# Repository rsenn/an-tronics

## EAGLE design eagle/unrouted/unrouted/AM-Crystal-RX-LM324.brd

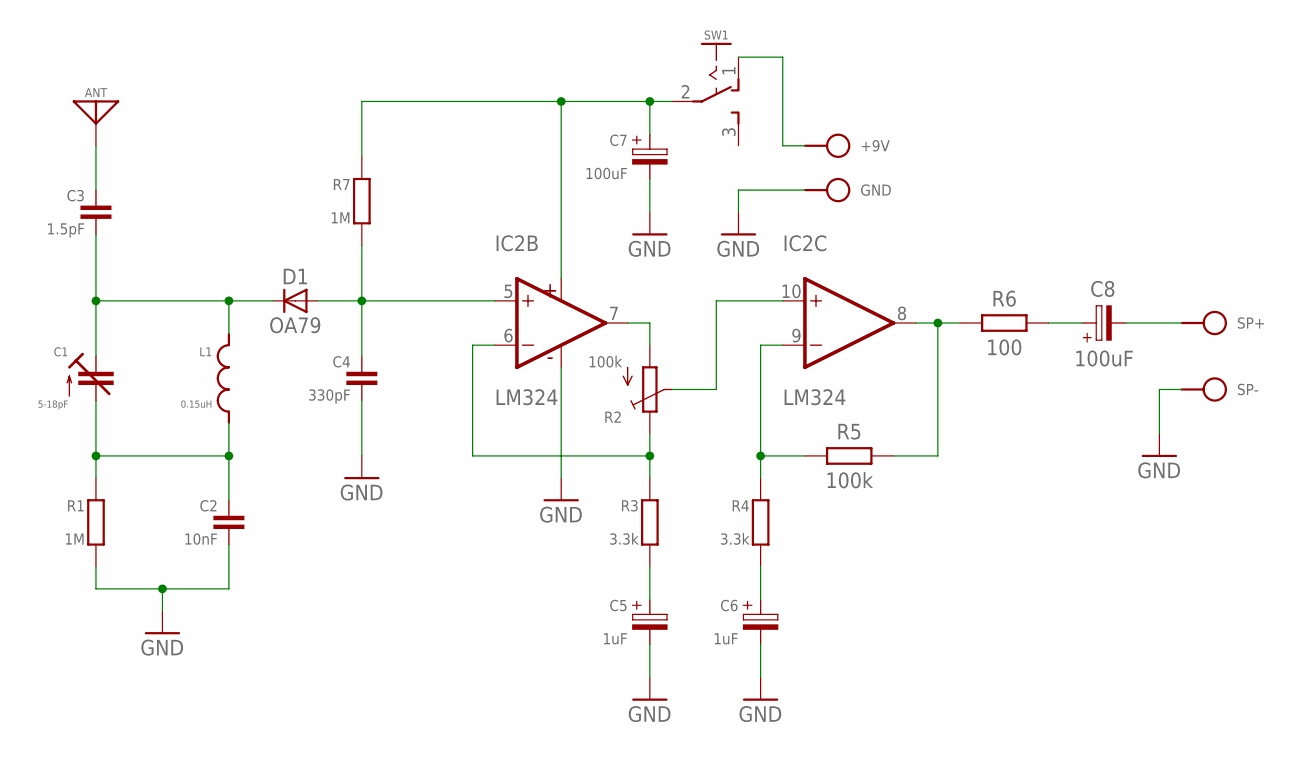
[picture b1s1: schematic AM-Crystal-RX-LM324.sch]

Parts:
+9V: BAT+; SPAD
ANT: ANT; SPAD
C1: 5-18pF; TRIM-2222-808
C2: 10nF; C050-025X075/V
C3: 1.5pF; C050-020X036
C4: 330pF; C050-024X044/V
C5: 1uF; E2.5-4/V
C6: 1uF; E2,5-3/V
C7: 100uF; E5-5/V
C8: 100uF; E2,5-5/V
D1: OA79; OA79-18/V
GND: BAT-; SPAD
IC2: LM324; DIL14
L1: 0.15uH; L-04-5/5
R1, R7: 1M; 0202/7-V
R2: 100k; B64Y
R3: 3.3k; 0202/7
R4: 3.3k; 0202/7-V
R5: 100k; 0202/7-V
R6: 100; 0202/7-V
SP+: SPKR+; SPAD
SP-: SPKR-; SPAD
SW1: SL-SW-1P-2T-H; SLSW-1P2T-H

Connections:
A: IC2.7 (OUT), R2.A
E: IC2.6 (-IN), R2.E, R3.1
GND: C2.2, C4.2, C5.-, C6.-, C7.-, GND.1, IC2.11 (V-), R1.2, SP-.1
unnamed: C4.1, D1.A, IC2.5 (+IN), R7.2
unnamed: C7.+, IC2.4 (V+), R7.1, SW1.2
unnamed: C1.1 (A), C2.1, L1.1, R1.1
unnamed: C1.2 (E), C3.2, D1.C, L1.2
unnamed: ANT.1, C3.1
unnamed: IC2.8 (OUT), R5.2, R6.1
unnamed: IC2.9 (-IN), R4.1, R5.1
unnamed: C5.+, R3.2
unnamed: C6.+, R4.2
unnamed: C8.+, R6.2
unnamed: C8.-, SP+.1
unnamed: +9V.1, SW1.1 (O)
S: IC2.10 (+IN), R2.S

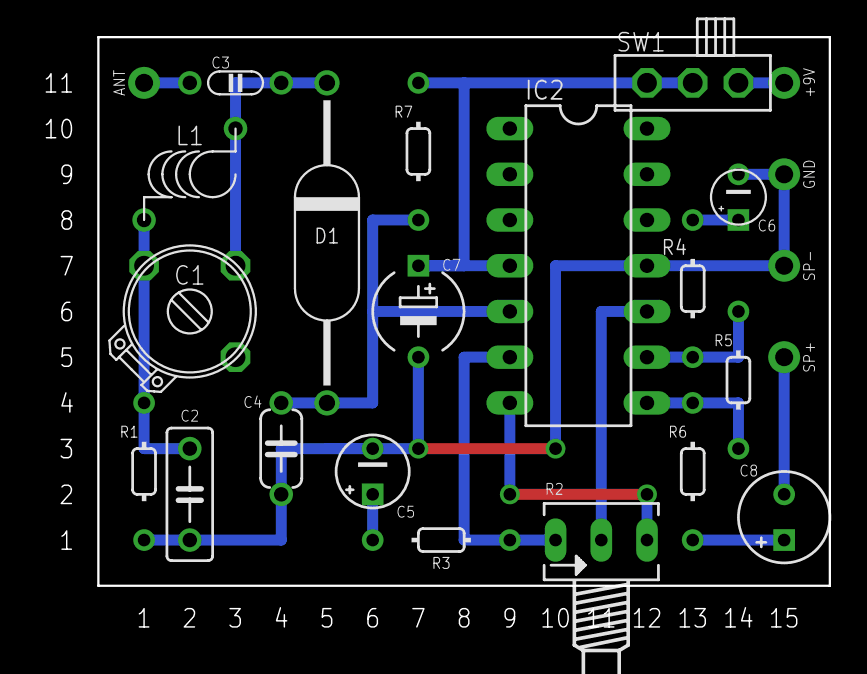
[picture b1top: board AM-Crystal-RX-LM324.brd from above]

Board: 2 copper layers, 40.6 x 30.5 mm, 24 parts (0 on the bottom side), 16 nets.

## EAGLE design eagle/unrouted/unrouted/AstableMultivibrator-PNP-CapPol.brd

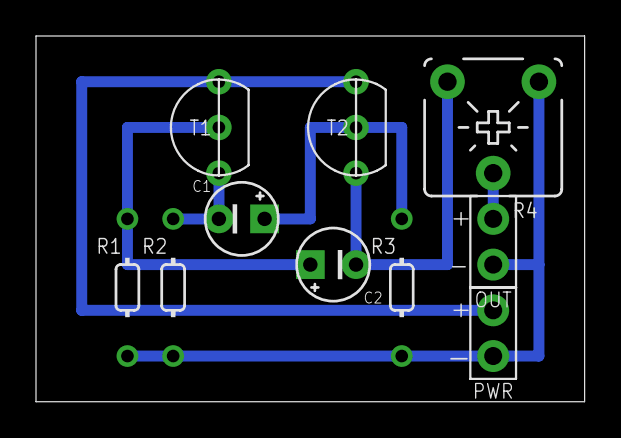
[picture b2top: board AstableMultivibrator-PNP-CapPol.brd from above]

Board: 2 copper layers, 30.5 x 20.3 mm, 10 parts (0 on the bottom side), 7 nets.

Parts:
C1, C2: 10uF; E2,5-4
J1: PWR-L
OUT: SPAD+--+; SPAD-+
R1, R3: 47k; 0202/7-V
R2: 5.1k; 0202/7-V
R4: 5k; POT-V
T1, T2: BC557; TO92-CBE

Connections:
GND: J1.1, OUT.1, R1.1, R2.1, R3.1, R4.A
unnamed: C2.-, R4.E, T2.C
unnamed: C1.-, R2.2, T1.C
unnamed: C2.+, R1.2, T1.B
unnamed: C1.+, R3.2, T2.B
unnamed: OUT.2, R4.S
VCC: J1.2, T1.E, T2.E

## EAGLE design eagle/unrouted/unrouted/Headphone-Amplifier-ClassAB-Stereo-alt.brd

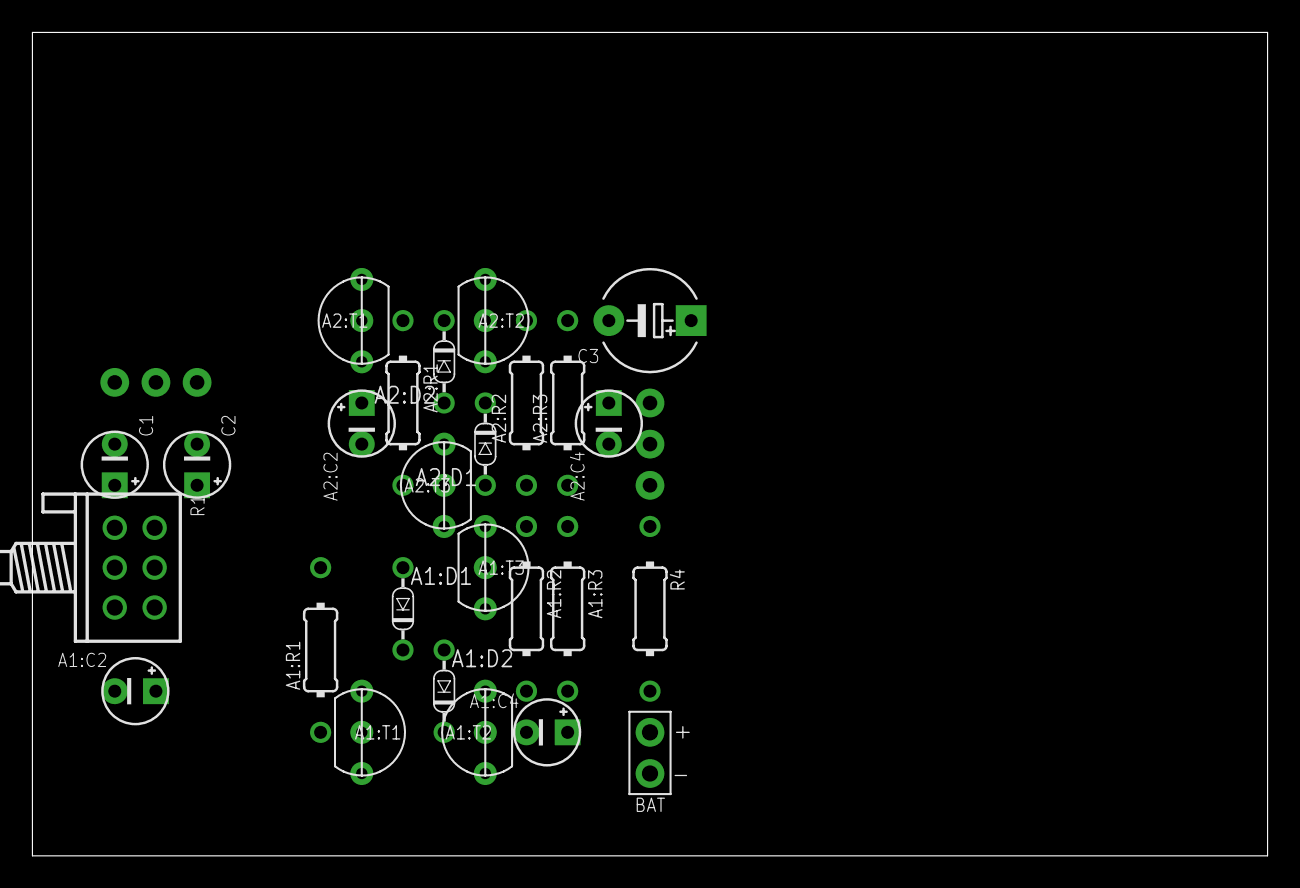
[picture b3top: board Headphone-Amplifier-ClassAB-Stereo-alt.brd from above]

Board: 2 copper layers, 76.2 x 50.8 mm, 28 parts (0 on the bottom side), 21 nets, no tracks yet.

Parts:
A1:C2, A2:C2: 4.7uF; E2,5-4
A1:C4, A2:C4: 220uF; E2,5-4
A1:D1, A1:D2, A2:D1, A2:D2: 1N4148; DO34-5V
A1:R1, A2:R1: 100k; 0204/10
A1:R2, A2:R2: 330; 0204/10
A1:R3, A2:R3: 100; 0204/10
A1:T1, A1:T3, A2:T1, A2:T3: BC547; TO92-CBE
A1:T2, A2:T2: BC557; TO92-CBE
BAT: SPAD+-+-; SPAD+-
C1, C2: 4.7uF; E2,5-4
C3: 100-1000uF; E5-6
IN: SAUDIO; SPAD-3
OUT: SAUDIO; SPAD-3
R1: POT-STEREO; POT-STEREO-2X3
R4: 22; 0204/10

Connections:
+3V: BAT.2, R4.2
A1:N$1: A1:D1.A, A1:R2.1, A1:T3.B
A1:N$2: A1:D2.C, A1:T1.C, A1:T2.B
A1:N$3: A1:D1.C, A1:D2.A
A1:N$4: A1:C4.-, A1:R1.2, A1:T2.E, A1:T3.E
A1:N$7: A1:C2.+, A1:R1.1, A1:T1.B
A2:N$1: A2:D1.A, A2:R2.1, A2:T3.B
A2:N$2: A2:D2.C, A2:T1.C, A2:T2.B
A2:N$3: A2:D1.C, A2:D2.A
A2:N$4: A2:C4.-, A2:R1.2, A2:T2.E, A2:T3.E
A2:N$7: A2:C2.+, A2:R1.1, A2:T1.B
GND: A1:T1.E, A1:T2.C, A2:T1.E, A2:T2.C, BAT.1, C3.-, IN.2, OUT.2, R1.1-E, R1.2-E
unnamed: A1:R3.1, A1:T3.C, A2:R3.1, A2:T3.C, C3.+, R4.1
unnamed: A1:C4.+, A1:R2.2, A1:R3.2, OUT.1
unnamed: C2.-, IN.3
unnamed: C2.+, R1.2-A
unnamed: C1.+, R1.1-A
unnamed: A1:C2.-, R1.1-S
unnamed: A2:C2.-, R1.2-S
unnamed: A2:C4.+, A2:R2.2, A2:R3.2, OUT.3
unnamed: C1.-, IN.1

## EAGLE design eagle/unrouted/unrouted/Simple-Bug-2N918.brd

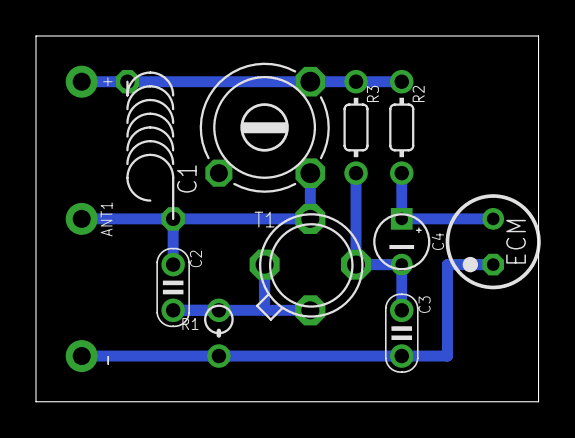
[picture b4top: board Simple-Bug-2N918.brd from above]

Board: 2 copper layers, 27.9 x 20.3 mm, 13 parts (0 on the bottom side), 6 nets.

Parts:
+: SPAD
ANT1: ANT; SPAD
C1: C-TR-PH20127-45-2P23; TRIM808-45
C2: 4.7pF; C025-020X036
C3: 1nF; C025-020X036
C4: E2,5-3
ECM: ECM-5
L1: 1uH; L-04/7
R1: 0202V
R2: 22k; 0202/5
R3: 47k; 0202/5
T1: 2N918; TO72-A45
̶̶: SPAD

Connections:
+UB: +.1, C1.1, L1.1, R2.1, R3.1
GND: C3.2, ECM.1, R1.1, ̶̶.1
unnamed: ANT1.1, C1.2, C2.1, L1.2, T1.3
unnamed: C2.2, R1.2, T1.1
unnamed: C3.1, C4.-, R3.2, T1.2
unnamed: C4.+, ECM.2, R2.2

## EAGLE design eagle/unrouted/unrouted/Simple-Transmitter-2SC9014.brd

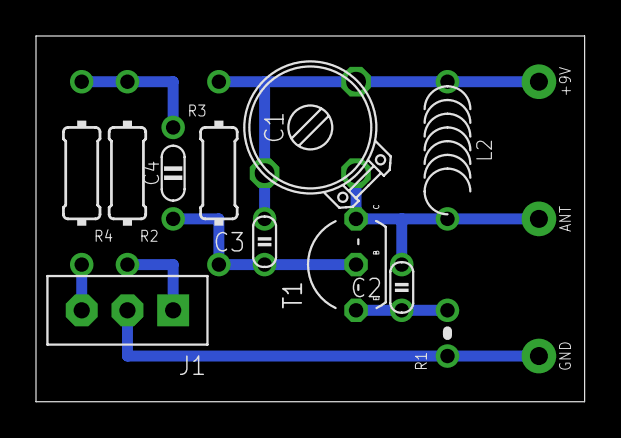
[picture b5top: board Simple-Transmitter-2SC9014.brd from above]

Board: 2 copper layers, 30.5 x 20.3 mm, 14 parts (0 on the bottom side), 8 nets.

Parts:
+9V: SPAD
ANT: ANT; SPAD
C1: 1.6-15pF; TRIM-2222-808
C2: 4.7pF; C025-015X024
C3: 1nF; C025-015X024
C4: 10nF; C050-020X036/V
GND: SPAD
J1: CONN-3P-3P; CONN-3P
L2: 1uH; L-04/7
R1: 100; 0204/2V
R2, R4: 47k; 0204/10-V
R3: 10k; 0204/10-V
T1: 2SC9014; TO92-EBC

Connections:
+UB: +9V.1, C1.3, C3.1, L2.2, R3.1
GND: GND.1, J1.2, R1.1
unnamed: J1.3, R4.1
unnamed: ANT.1, C1.2, C2.1, L2.1, T1.C
unnamed: C2.2, R1.2, T1.E
unnamed: J1.1, R2.1
unnamed: C3.2, C4.1, R3.2, T1.B
unnamed: C4.2, R2.2, R4.2

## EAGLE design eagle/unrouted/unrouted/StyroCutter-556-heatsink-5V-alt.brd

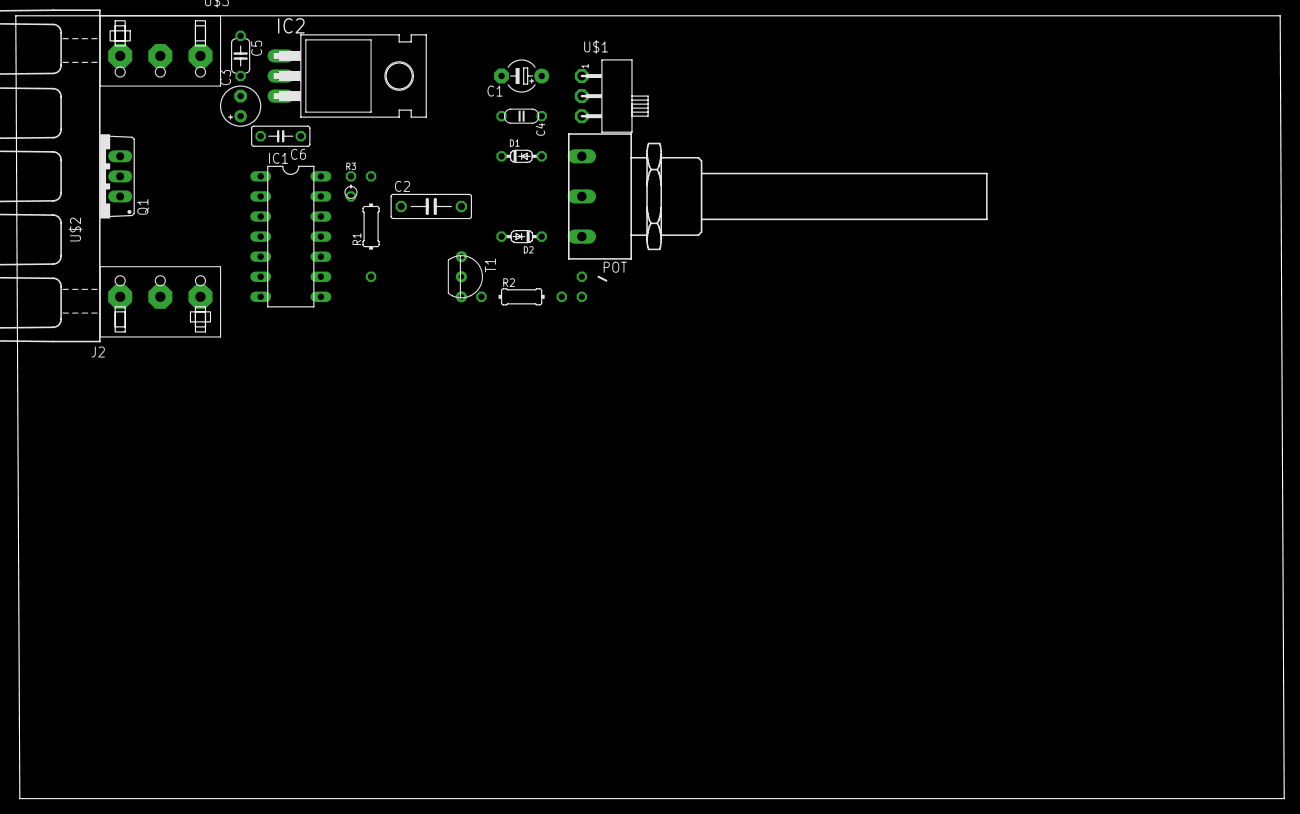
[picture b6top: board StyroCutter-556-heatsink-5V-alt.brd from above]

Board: 2 copper layers, 160.5 x 99.1 mm, 21 parts (1 on the bottom side), 14 nets, no tracks yet.

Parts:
C1: 10uF; E5-4
C2: 10nF; C075-032X103
C3: 47uF/35V; E2,5-5
C4: 100nF; C050-020X036
C5: 0.33uF; C050-024X044
C6: 0.1uF; C050-025X075
D1, D2: 1N4148; DO34-5
IC1: NE556; DIL14
IC2: 7805T; TO220H
J2: PCON3_MIGROS; CON-MIGROS-3PIN
POT: 4.7k; PC16S
Q1: IRFB3207ZPbF; TO220BV
R1: 10k; 0204/12
R2: 1k; 0204/10
R3: 1k; 0202/2V
T1: BC547; TO92-CBE
U$1: SL-SW-1P-2T-V; SLSW-1P2T-V
U$2: AQ; AQ_HS_3A
U$3: PCON3; CON-MIGROS-3PIN
U$4: LED-3MM-V

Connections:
+12V: C5.1, IC2.1, J2.3, U$3.1
GND: C1.-, C2.1, C3.-, C4.1, C5.2, C6.2, IC1.3, IC1.4, IC1.6, IC1.7, IC2.2, Q1.S, U$3.2, U$3.3, U$4.C
unnamed: D2.C, POT.1A
unnamed: D1.A, POT.1E
unnamed: IC1.9, R1.1, T1.B
unnamed: C4.2, U$1.3
unnamed: C2.2, IC1.11
unnamed: IC1.13, POT.1S, R3.1
unnamed: Q1.G, R2.1, T1.E
unnamed: D1.C, D2.A, IC1.8, IC1.12, U$1.2
unnamed: C1.+, U$1.1
unnamed: R2.2, U$4.A
PWM: J2.1, J2.2, Q1.D
V+: C3.+, C6.1, IC1.10, IC1.14, IC2.3, R1.2, R3.2, T1.C

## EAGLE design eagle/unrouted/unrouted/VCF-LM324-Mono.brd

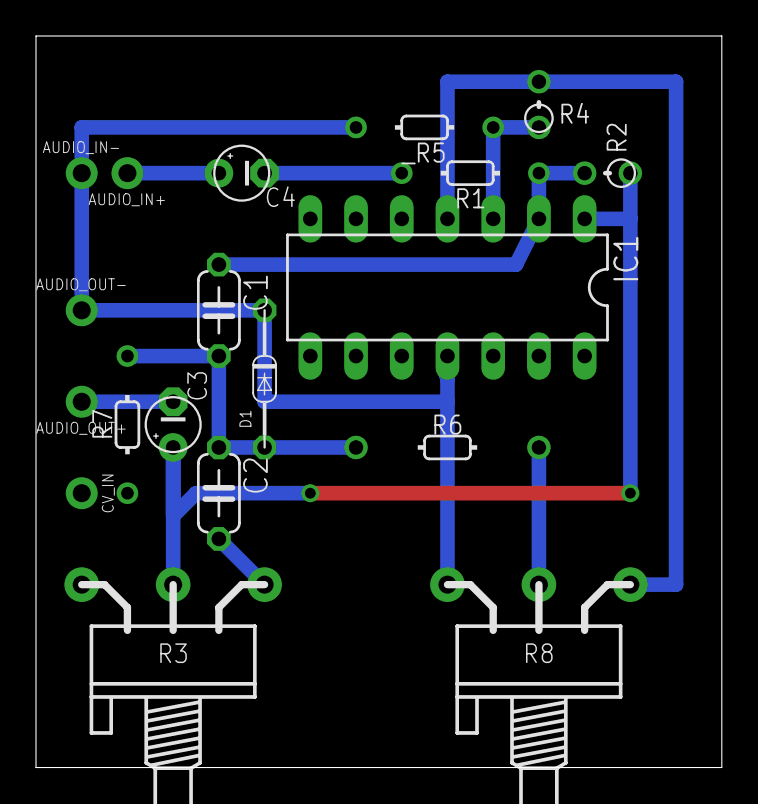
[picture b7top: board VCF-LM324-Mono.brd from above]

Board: 2 copper layers, 38.1 x 40.6 mm, 19 parts (0 on the bottom side), 12 nets.

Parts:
AUDIO_IN+: AUDIO_IN; SPAD
AUDIO_IN-: SPAD
AUDIO_OUT+: AUDIO_OUT; SPAD
AUDIO_OUT-: SPAD
C1, C2: 100nF; C050-024X044
C3, C4: 1uF; E2,5-3
CV_IN: CV_IN; SPAD
D1: 1N4148; DO34-7
IC1: LM324; DIL14
R1: 470k; 0202/7
R2, R4: 100k; 0202V
R3: 10k; POT-P5
R6: 1k; 0202/10
R7: 1k; 0202/7
R8: 100k; POT-P5
_R5: 100k; 0202/7

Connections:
GND: AUDIO_IN-.1, AUDIO_OUT-.1, D1.C, IC1.11, R8.A, _R5.1
unnamed: AUDIO_IN+.1, C4.+
unnamed: C1.1, IC1.2, R1.2, R2.1
unnamed: C2.2, R3.E
unnamed: C3.+, IC1.1, R2.2, R3.S
unnamed: R6.2, R8.S
unnamed: AUDIO_OUT+.1, C3.-
unnamed: IC1.3, R4.2, _R5.2
unnamed: CV_IN.1, R7.2
unnamed: C1.2, C2.1, D1.A, R6.1, R7.1
unnamed: C4.-, R1.1
VCC: IC1.4, R4.1, R8.E

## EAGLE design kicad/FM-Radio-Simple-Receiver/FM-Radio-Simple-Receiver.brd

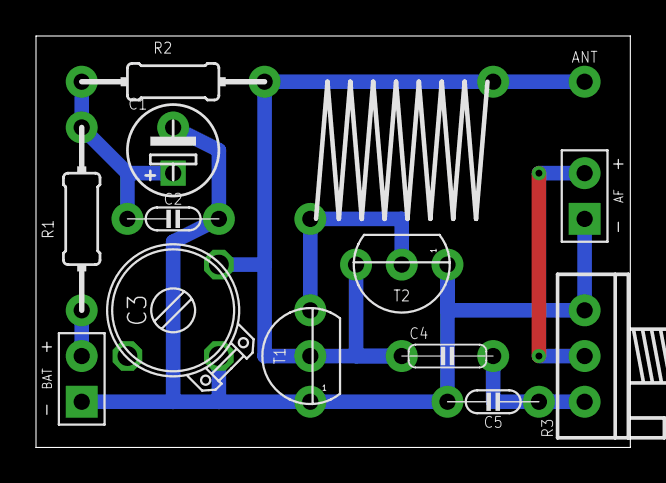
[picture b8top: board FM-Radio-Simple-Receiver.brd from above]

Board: 2 copper layers, 33.0 x 22.9 mm, 14 parts (0 on the bottom side), 7 nets.

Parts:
AF: SPAD+-+-; SPAD+-
ANT: ANT; SPAD
BAT: VCC_GNDL; SPAD-+
C1: 100µF; E2,5-5/V
C2: 100nF; C050-020X036/V
C3: 2 - 20pF; TRIM-2222-808
C4: 220nF; C050-020X044
C5: 2.2nF; C050-020X036/V
L1: 0.2µH; L-10/10X
R1: 1kΩ; 0204/10
R2: 10kΩ; 0204/10
R3: 10kΩ; POT
T1, T2: 2N2222; TO92

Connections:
GND: AF.1, BAT.1, C1.-, C2.2, C3.2, C5.2, R3.E, T1.1, T2.1
unnamed: ANT.1, C3.3, C4.1, L1.P$1, R2.2, T1.2, T2.3
unnamed: C1.+, C2.1, R1.2, R2.1
unnamed: C4.2, C5.1, R3.A
unnamed: L1.P$2, T1.3, T2.2
unnamed: AF.2, R3.S
VCC: BAT.2, R1.1
